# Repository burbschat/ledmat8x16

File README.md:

# *LTP-12188M-08* Based Two Color 8x16 LEDs in 8x8 Slots LED Matrix Display Module

## Motivation
Found a place that sold their dead stock of *LTP-12188M-08* modules for
extremely cheap and bought a whole bunch.
To drive those I would like to have a minimal and cheap solution which is also
modular, meaning I can build an (for any practical purposes) arbitrarily sized
display by just assembling identical modules (and perhaps a few cables etc.).

## Pictures
### Renders
Had some fun with [this incredible
tool](https://github.com/30350n/pcb2blender). Shown renders are of the first
version of the single tile driver board.
There is a newer revision with extra features for mouting as well as a *blade*
version where 8 modules are combined into one long board, as that is a much
more reasonable solution for large displays.

| Front                                                              | Back                                                              | Oblique
| ------------------------------------------------------------------ | ----------------------------------------------------------------- | ---------------------------------------------------------------------- |
|  |  |  |

### Prototype
Testing three prototype modules driven by a Raspberry Pi Pico (which is
debugged from a second Pico via SWD).
The colors do look much more vibrant in person. Also, the apparent differences
in brightness are an artifact of the way this picture was captured.

A second test now using the controller and row connect boards for a double row
display. Again, the colors look much better in person than on this picture.
This can now display much larger frames as well as animations (cycling through
a given number of frames in a buffer on the pico). For faster data transfer a
serial interface over USB is used (previously UART through the debug probe was
used, which is much slower).
A debug probe is still attached for, well, debugging. But the device now can be
used without it.

## Parts
* *LTP-12188M-08* (8x8 two-color (red/green) LED dot matrix)
* *TLC59283* (16 channel constant current LED driver with pre-charge FET)
    * Seems to be cheapest LED driver available
    * No dimming supported but perhaps possible by updating the frames at a high enough rate
    * Can be daisy chained
    * Up to 32MHz operation advertised
        * One frame is 8 rows x 16 bits = 128 transfers. At 32MHz one transfer
        takes 3.125e-08s so 4e-6s per frame per tile. For 60 tiles thats
        240e-6s for the whole panel. If we want 60 frames per second
        (16.666e-3s per frame), we can sub-divide each frame into 69 sections
        for which a pixel can be either on or off. Thus a 69 level brightness
        adjustment may be possible.
* *DMP31D7LDW-13* (dual p-channel enhancement mode MOSFET)
    * Seems to be the cheapest on DigiKey with ~500ma sustained current
    * Should switch fast enough
        * NTZD3152P may be a faster alternative, but tolerates less peak
        current (sustained currents is similar though)
* Board connectors
    * DigiKey
        * *Ph2ra-16-ua*
            * cheapest on DigiKey
            * mating connector from same manufacturer seems to be rs2br-16-g? but
            this is not readily available and of odd shape...
        * *pptc082ljbn-rc*
            * Cheapest mating connector on DigiKey
        * *Consider buying those from lcsc where they should be much cheaper*
    * LCSC
        * *2541WR-2x08P*
            * Extremely cheap
        * *PM254-2-08-W-8.5*
            * Mating part from same manufacturer: PZ254-2-08-W-8.5

### Notes
* There seems to be no cheap LED driver which supports row *and* column driving
    * IS31FL3731 seems to be pretty capable. Costs a little more but is still
    affordable. However, choosing the simpler part will surely teach one more
    things than just buying the solution.

#### LED Currents
* Use 5V supply
    * The TLC59283 are constant current and support up to 10V
        * The constant-current value of all 16 channels is set by a single external resistor
    * 3.3V may also work, but may be insufficient for some chips, so use 5V
* Peak forward current is 60mA/90mA (green/red)
    * 16 columns (8 red 8 green) on one row so peak current of 1200 mA per row
* Average current is 25mA (same for both colors)
    * Total of 400mA average current per row (if all 16 channels are on)
    * A 500mA sustained/1.2A peak driver should be sufficient
    * In actual operation the rows are multiplexed so actually only about an
    eight of the average current is expected. So actually 400mA sustained
    current per tile if all LEDs are on.
    * Eventually set the current limit at the TLC59283 to around 25mA
        * 2k resistor should give 26.5mA, which is alright
* Want row drivers separately for each tile to avoid driver current scaling
with number of tiles
    * Make sure that connections between tiles support high enough currents
* Consider [MOSFET arrays](https://www.digikey.com/en/products/filter/transistors/fets-mosfets/fet-mosfet-arrays/289)
as we need 8 of them per tile
    * Need P-channel to drive by setting gate voltage low (below source voltage)
    * Maybe not too long rise/fall times 
    * DMP31D7LDW-13 seems fine (20JPY at 200 pieces, doesn't seem to get much cheaper on digikey)
        * There are many SOT-363 options so if this one does not work, one can
        probably find a pin compatible alterative
    * [Search on digikey](https://www.digikey.jp/en/products/filter/transistors/fets-mosfets/fet-mosfet-arrays/289?s=N4IgjCBcoEwAwHYqgMZQGYEMA2BnApgDQgD2UA2iAgMwAcCALEsWDPHHCC2xzCALrEADgBcoIAMoiATgEsAdgHMQAX2IA2OLWQg0kLHiKkKIGGFoBWauq6nrNBrZj2rThq2p9iMBvHXU3ajAATgDvBiDgm2IEdVoYC2CnCwtLMNMUy21vVNiLZODguGjTdWc4p38IkpgEGGDUpwQLLUdvWlC2JyKEUO6YeLbTYIGE7uCwFNswEIQ62wZaScSFsGavEHdm9MXl7M2WmlsWos5iCwGwEpS4d2OWxvPGanTE53TNEYgNWvrp9WawSGV1iYHSrABYGBMEh%2B1YtCY%2BW4CLm01qCCWaOCtABWPo33AQSsBLBkwYwKJDCSLBe7g2YIYiTh1g4JTBdQq3jgkyBTm5ZXS8CuL2mCHMCNFAz6LDqHTZssKouoUWBjCiJLV8xlmkx2q08o5SJA8TycIxMKNayKUxl1up4FovGYDo4nictRCGzYdUQfM0NtMxTgFmd2xoBL8jpqiHJ9vgjBWXPidD5gyGvVY5lTCSN8BGCDOpjA3LBTmLM2dZmK8TLYM5RfZhZ8c2Kbjm1CGzcYleoWi0TiC1F6tlo1CsZQHzhCk5xPYY3M7HfccfUZXUEdXA32MP8t2S9VxOXnk2STHnp8YEcdBe3cVojsqIwf3gL7kFr66L7Wve6Q58v5oXNQnWJxRwRDZe0WRViEg61bFiVdfRg25QjjKIUiGHF6GdfwrUtBl1GBXw4CKf4ZjWaZRypcFRxaQtzDHeBklXGYBGEMRIEkGQFGUNQQAAWj4aBdCgGQAFcjDISBKCNJJ%2BD4-ikmEvRxMkkwIHkvibGE2QABNxH48tbFEcRbBEABPIR8HETBcDQFQVCAA)

#### Clock
The clock will have to arrive at each TLC59283 before the output of the
previous one had a chance to change. According to the data sheet, the delay
until SOUT changes is normally around 11ns. As we are only concerned about
adjacent modules in close proximity, the clock propagation delay should be well
below 10ns.
A possible concern mentioned [here](https://www.eevblog.com/forum/projects/shift-register-delay-tlc59283/msg5714097/#msg5714097)
is that the clock signal integrity may be degraded due to large capacitance if
we fan it out too far. To solve this we may employ a buffer, this however would
mean we need either a very fast buffer to not skew the clock relative to the
data signal too much, or also have to buffer the data signal at the same time.
Buffering two signals should be doable.
This is probably not an issue, but technically if the buffers are to slow, this
could limit the rate at which we can operate the panel (i.e. clock in data).
As, if it works, no buffers should be the easier solution, for now I'll try
without. If required, we may try to add clock line terminations to avoid
ringing.

## Mechanical Design
* Board interconnects using horizontal pin headers on the back of the board (tile is on the front)
    * 8 pins seem to fit just right, so two rows with 8 pins each seems to be a good choice
    * These also will provide mechanical support within each row
* Consider some sort of locating feature to use to locate modules in maybe a
3d-printed back plane or with small clips to be inserted between modules (**TODO**) 
    * Could shave off the corners and have short square (45 deg. rotated) posts on the back plane
    * High symmetry is probably a good thing so locating features on maybe only
    top/bottom may not be as useful as the shaved off corners
    * To assemble multiple rows such a locating feature would be required
    * For a large display with many rows and columns a backplane is probably mandatory
    
## Heat Dissipation
Found that when I run a fully lit frame (all 16 LEDs enabled while multiplexing
the rows) the whole module gets quite hot. Not entirely sure what produces the
heat. If it is the TLC59283, one could simply remove the solder mask on the
back side of the board which is a ground plane to which the ground pad on the
TLC59283 is connected to and place some sort of heat sink there.
This is of course the reason why the TLC59283 is placed under the LED matrix
module on the front and not at the back of the board and not simply attributed
to be not checking the orientation of the modules footprint before doing the
tedious routing which I do not want to do twice.
Will have to further check what is the source of the heat. However, as long as
the display is not constantly fully illuminated, it does not appear to get
excessively hot.

## Driving the Modules
I use an Raspberry Pi Pico (2 to be exact) to the modules. The serial interface
for the TLC59283 is implemented using a PIO state machine (with DMA) which can
clock out serial data independent of the processor cores and thus is a very
performant solution. Switching between the rows is done by the processor which
also feeds data from a global frame buffer to the DMA (which feeds it to the
PIO state machine).
Other microcontrollers will probably also work. Not sure how one would handle
the serial communication though. AT a slower rate one can perhaps just bit bang
using GPIO. Didn't try.
The code I use on the Pico is available in a separate repository [here](https://github.com/burbschat/ledmat8x16pico/).

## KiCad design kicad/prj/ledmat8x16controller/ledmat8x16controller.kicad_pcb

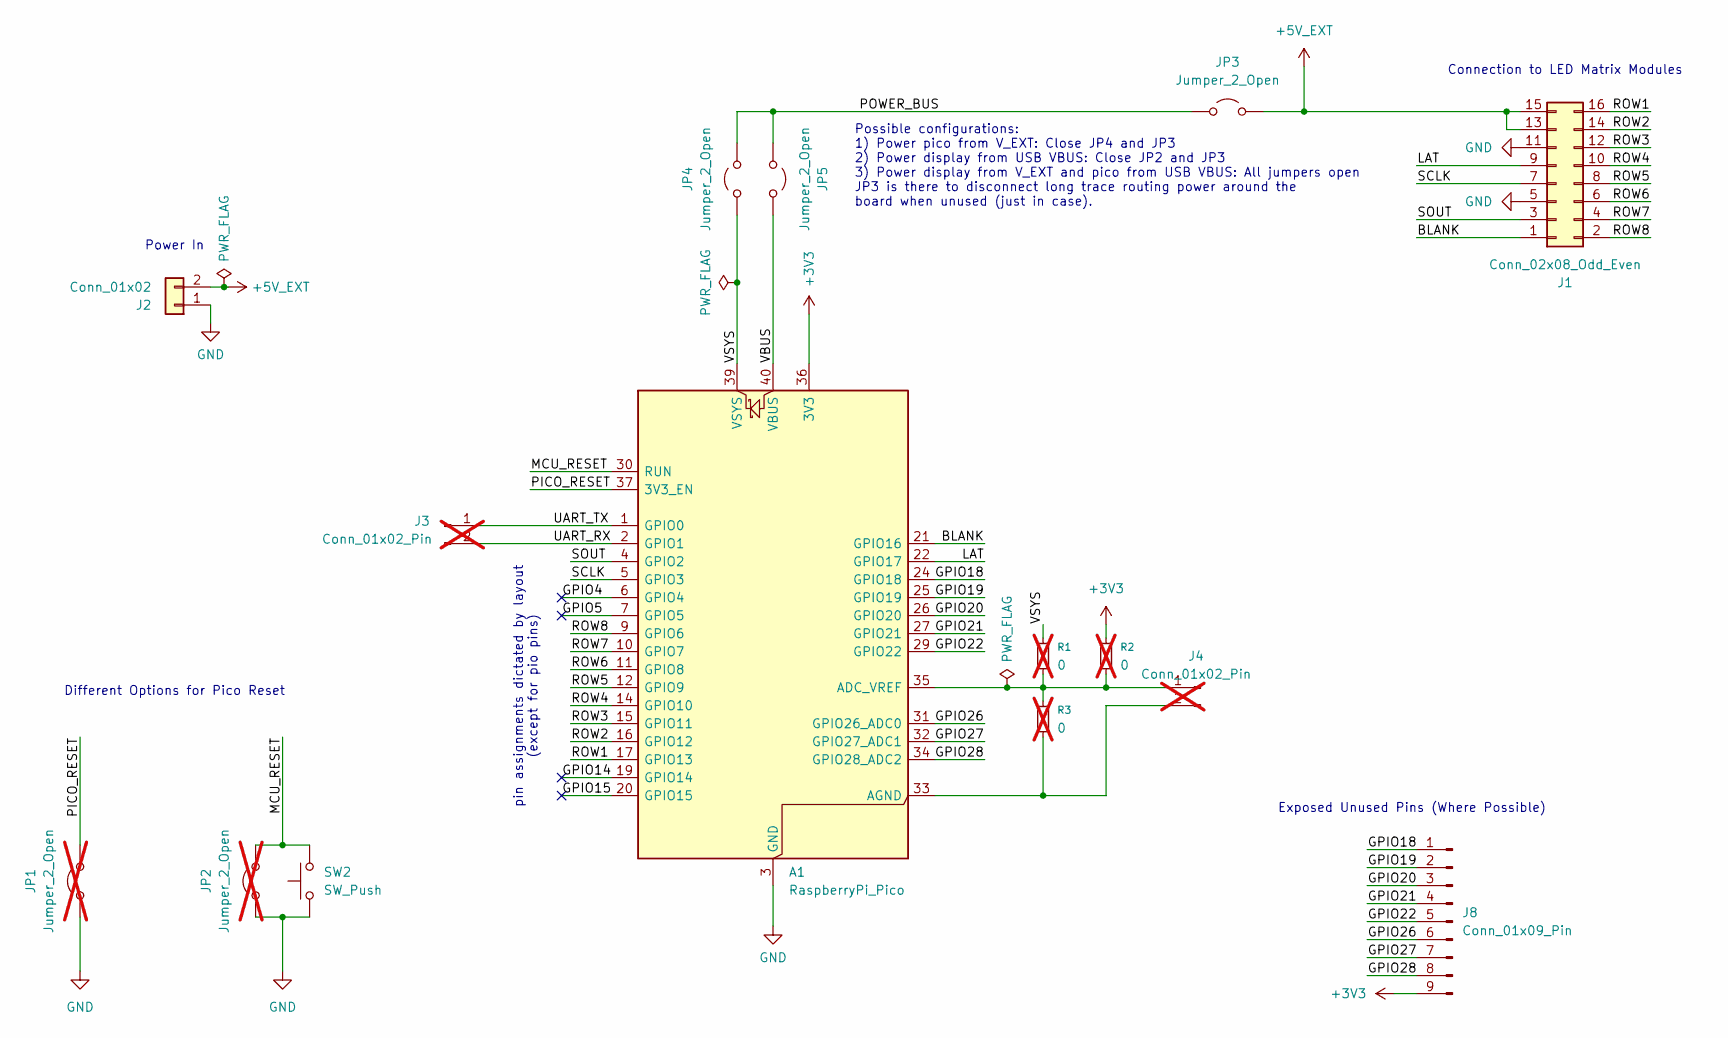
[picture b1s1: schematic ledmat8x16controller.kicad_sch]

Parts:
A1: RaspberryPi_Pico; RaspberryPi_Pico_Common_ProbablySocketed
J1: Conn_02x08_Odd_Even; PinSocket_2x08_P2.54mm_Horizontal
J2: Conn_01x02; TerminalBlock_Phoenix_PT-1,5-2-3.5-H_1x02_P3.50mm_Horizontal
J3, J4: Conn_01x02_Pin; PinHeader_1x02_P2.54mm_Vertical; not fitted
J8: Conn_01x09_Pin; PinHeader_1x09_P2.54mm_Vertical
JP1, JP2: Jumper_2_Open; TestPoint_2Pads_Pitch2.54mm_Drill0.8mm; not fitted
JP3, JP4, JP5: Jumper_2_Open; SolderJumper-2_P1.3mm_Open_RoundedPad1.0x1.5mm
R1, R2, R3: 0; R_0603_1608Metric_Pad0.98x0.95mm_HandSolder; not fitted
SW2: SW_Push; SW_SPST_SKQG_WithStem

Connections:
+3V3: A1.36 (3V3), J8.9, R2.1
+5V_EXT: J1.13, J1.15, J2.2, JP3.2 (B)
/BLANK: A1.21 (GPIO16), J1.1
/GPIO4: A1.6 (GPIO4)
/GPIO4_1: A1.6 (GPIO4)
/GPIO5: A1.7 (GPIO5)
/GPIO5_1: A1.7 (GPIO5)
/GPIO14: A1.19 (GPIO14)
/GPIO14_1: A1.19 (GPIO14)
/GPIO15: A1.20 (GPIO15)
/GPIO15_1: A1.20 (GPIO15)
/GPIO18: A1.24 (GPIO18), J8.1
/GPIO19: A1.25 (GPIO19), J8.2
/GPIO20: A1.26 (GPIO20), J8.3
/GPIO21: A1.27 (GPIO21), J8.4
/GPIO22: A1.29 (GPIO22), J8.5
/GPIO26: A1.31 (GPIO26_ADC0), J8.6
/GPIO27: A1.32 (GPIO27_ADC1), J8.7
/GPIO28: A1.34 (GPIO28_ADC2), J8.8
/LAT: A1.22 (GPIO17), J1.9
/MCU_RESET: A1.30 (RUN), JP2.2 (B), SW2.2
/PICO_RESET: A1.37 (3V3_EN), JP1.2 (B)
/POWER_BUS: JP3.1 (A), JP4.2 (B), JP5.2 (B)
/ROW1: A1.17 (GPIO13), J1.16
/ROW2: A1.16 (GPIO12), J1.14
/ROW3: A1.15 (GPIO11), J1.12
/ROW4: A1.14 (GPIO10), J1.10
/ROW5: A1.12 (GPIO9), J1.8
/ROW6: A1.11 (GPIO8), J1.6
/ROW7: A1.10 (GPIO7), J1.4
/ROW8: A1.9 (GPIO6), J1.2
/SCLK: A1.5 (GPIO3), J1.7
/SOUT: A1.4 (GPIO2), J1.3
/UART_RX: A1.2 (GPIO1), J3.2
/UART_TX: A1.1 (GPIO0), J3.1
/VBUS: A1.40 (VBUS), JP5.1 (A)
/VSYS: A1.39 (VSYS), JP4.1 (A), R1.1
GND: A1.3 (GND), A1.8 (GND), A1.13 (GND), A1.18 (GND), A1.23 (GND), A1.28 (GND), A1.38 (GND), J1.5, J1.11, J2.1, JP1.1 (A), JP2.1 (A), SW2.1
unnamed: A1.35 (ADC_VREF), J4.1, R1.2, R2.2, R3.1
unnamed: A1.33 (AGND), J4.2, R3.2

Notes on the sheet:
Exposed Unused Pins (Where Possible)
Connection to LED Matrix Modules
Possible configurations: 1) Power pico from V_EXT: Close JP4 and JP3 2) Power display from USB VBUS: Close JP2 and JP3 3) Power display from V_EXT and pico from USB VBUS: All jumpers open JP3 is there to disconnect long trace routing power around the board when unused (just in case).
pin assignments dictated by layout (except for pio pins)
Power In
Different Options for Pico Reset

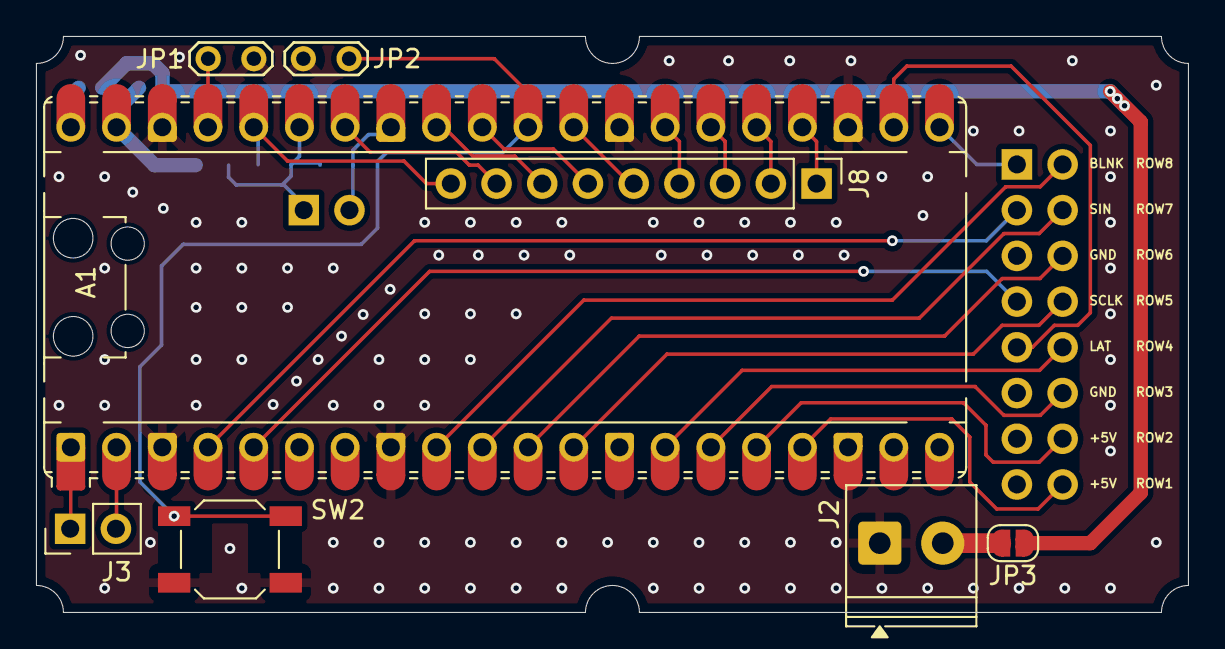
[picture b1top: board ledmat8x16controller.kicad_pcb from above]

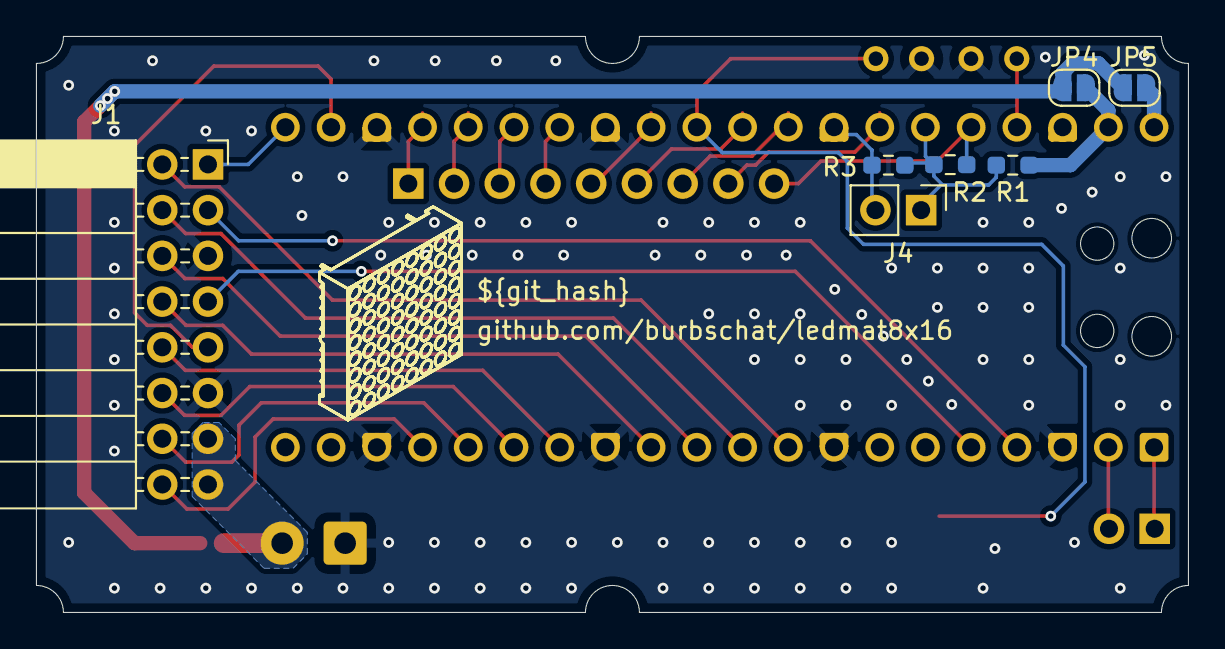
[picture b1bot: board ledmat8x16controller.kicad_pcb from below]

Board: 2 copper layers, 64.0 x 32.0 mm, 15 parts (7 on the bottom side), 32 nets.

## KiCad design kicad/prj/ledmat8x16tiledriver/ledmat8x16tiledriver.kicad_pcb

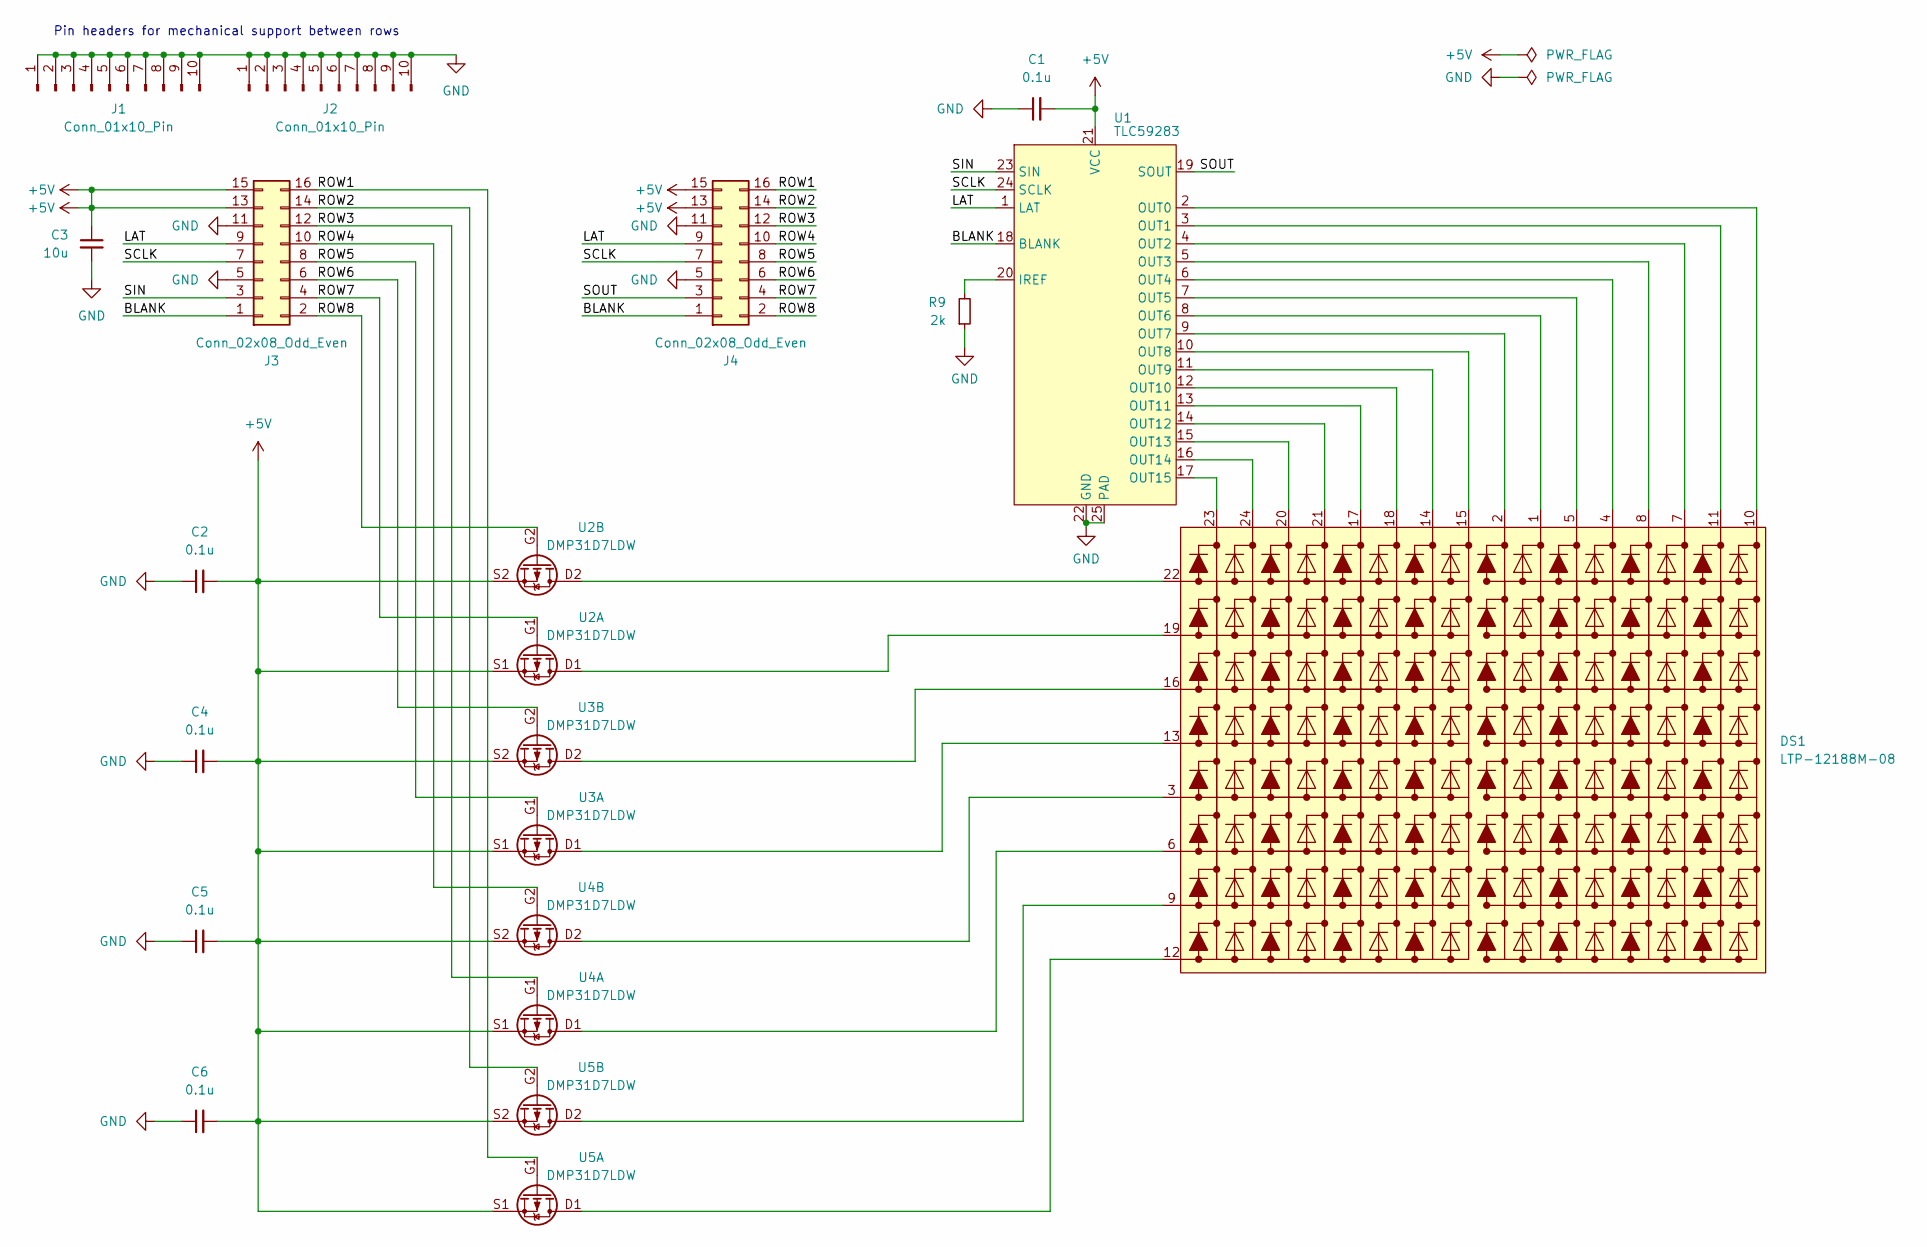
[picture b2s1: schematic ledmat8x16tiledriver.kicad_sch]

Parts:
C1, C2, C4, C5, C6: 0.1u; C_0603_1608Metric_Pad1.08x0.95mm_HandSolder
C3: 10u; C_0805_2012Metric_Pad1.18x1.45mm_HandSolder
DS1: LTP-12188M-08
J1, J2: Conn_01x10_Pin; PinHeader_1x10_P2.54mm_Vertical
J3: Conn_02x08_Odd_Even; PinHeader_2x08_P2.54mm_Horizontal
J4: Conn_02x08_Odd_Even; PinSocket_2x08_P2.54mm_Horizontal
R9: 2k; R_0603_1608Metric_Pad0.98x0.95mm_HandSolder
U1: TLC59283; Texas_RGE0024C_VQFN-24-1EP_4x4mm_P0.5mm_EP2.1x2.1mm
U2, U3, U4, U5: DMP31D7LDW; SOT-363_SC-70-6

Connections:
+5V: C1.2, C2.2, C3.1, C4.2, C5.2, C6.2, J3.13, J3.15, J4.13, J4.15, U1.21 (VCC), U2.S1, U2.S2, U3.S1, U3.S2, U4.S1, U4.S2, U5.S1, U5.S2
/BLANK: J3.1, J4.1, U1.18 (BLANK)
/LAT: J3.9, J4.9, U1.1 (LAT)
/ROW1: J3.16, J4.16, U5.G1
/ROW2: J3.14, J4.14, U5.G2
/ROW3: J3.12, J4.12, U4.G1
/ROW4: J3.10, J4.10, U4.G2
/ROW5: J3.8, J4.8, U3.G1
/ROW6: J3.6, J4.6, U3.G2
/ROW7: J3.4, J4.4, U2.G1
/ROW8: J3.2, J4.2, U2.G2
/SCLK: J3.7, J4.7, U1.24 (SCLK)
/SIN: J3.3, U1.23 (SIN)
/SOUT: J4.3, U1.19 (SOUT)
GND: C1.1, C2.1, C3.2, C4.1, C5.1, C6.1, J1.1, J1.2, J1.3, J1.4, J1.5, J1.6, J1.7, J1.8, J1.9, J1.10, J2.1, J2.2, J2.3, J2.4, J2.5, J2.6, J2.7, J2.8, J2.9, J2.10, J3.5, J3.11, J4.5, J4.11, R9.1, U1.22 (GND), U1.25 (PAD)
unnamed: DS1.3, U4.D2
unnamed: DS1.6, U4.D1
unnamed: DS1.9, U5.D2
unnamed: DS1.12, U5.D1
unnamed: DS1.13, U3.D1
unnamed: DS1.16, U3.D2
unnamed: DS1.19, U2.D1
unnamed: DS1.22, U2.D2
unnamed: R9.2, U1.20 (IREF)
unnamed: DS1.10, U1.2 (OUT0)
unnamed: DS1.11, U1.3 (OUT1)
unnamed: DS1.7, U1.4 (OUT2)
unnamed: DS1.8, U1.5 (OUT3)
unnamed: DS1.4, U1.6 (OUT4)
unnamed: DS1.5, U1.7 (OUT5)
unnamed: DS1.1, U1.8 (OUT6)
unnamed: DS1.2, U1.9 (OUT7)
unnamed: DS1.15, U1.10 (OUT8)
unnamed: DS1.14, U1.11 (OUT9)
unnamed: DS1.18, U1.12 (OUT10)
unnamed: DS1.17, U1.13 (OUT11)
unnamed: DS1.21, U1.14 (OUT12)
unnamed: DS1.20, U1.15 (OUT13)
unnamed: DS1.24, U1.16 (OUT14)
unnamed: DS1.23, U1.17 (OUT15)

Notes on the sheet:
Pin headers for mechanical support between rows

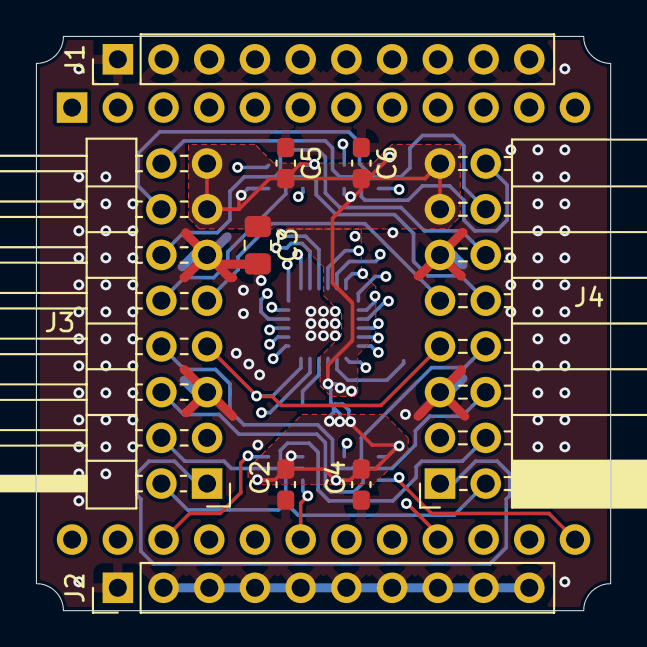
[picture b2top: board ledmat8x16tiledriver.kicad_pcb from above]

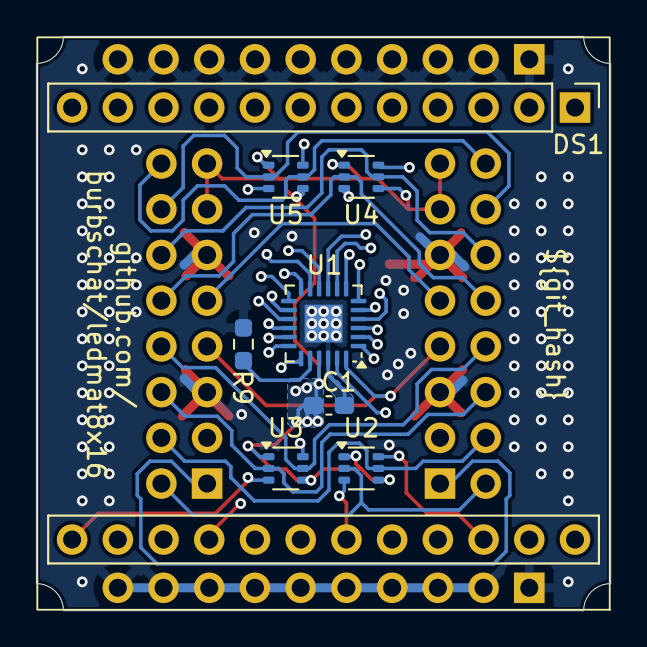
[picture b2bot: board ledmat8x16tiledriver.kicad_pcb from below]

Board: 4 copper layers, 31.9 x 31.9 mm, 17 parts (8 on the bottom side), 40 nets.

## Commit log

2025-03-23 initial notes and collection of datasheets
2025-03-24 draw basic schematic
    some footprint assignment is still todo
2025-03-24 create/assign all footprints
2025-03-27 finish layout (witch a catch)
    I put the led matrix footprint on the wrong side of the board...
    This was fixed by moving the pin headers which however now results in
    the controller IC being under the led matrix module. Not what I wanted
    but not easy to fix. I wanted to use headers to mount the module anyways
    to there should be no interference. Try to use some short female pin
    headers (which apparently is a thing).
2025-04-13 re-route traces close to clock trace
    Clock appeared to couple into the closeby traces
2025-04-13 attempt to increase space between data and blank traces
    also observed coupling of data into the blank line.
2025-05-03 Fix empty value field for TLC59283
2025-05-03 Add 3d model for led matrix module
2025-05-03 Add 3d model for socketed version of the led matrix module
2025-05-03 Add license
2025-05-03 Add kibot config file
2025-05-03 Add some renders of the PCB
2025-05-03 Add another picture to readme and adjust layout of renders
2025-05-03 Adjust README title
2025-05-13 Fix wrong footprint type for led matrix module
2025-05-13 Update footprints in layout (including the led matrix module one)
2025-05-13 Cut little arcs into the corners for mounting modules with maybe M3 screws
    Or perhaps standoffs?
2025-05-13 Fix led modules footprint througholes out of alignment by 0.01mm
    Of course this does not really matter, but it bugs me.
2025-05-13 Add some holes for headers near the top/bottom edge
    Perhaps this can be used as a different way of mounting. Not sure, I'll
    have to try. Unfortunately the board dimensions did not allow for the
    spacing to be a multiple of 2.54mm. But positioning is such that between
    adjacent rows the headers should be exactly 2.54mm apart.
2025-05-13 Update small resistor symbol to match library
2025-05-16 Slight adjustments to zone fill and ground plane
2025-05-16 Update footprint to newer version (with smaller courtyard)
2025-05-16 Add repo url and git hash to silkscreen
    For traceability, but also just becasue it's possible.
    Substitution of git hash is done by kibot.
2025-05-18 Add files for a simple row interconnect board
2025-05-18 Indicate some of the important dimensions on the user drawings layer
2025-05-18 Add dimensions to interconnect board, fix silkscreen
2025-05-18 Fix slight asymetry in zone fill
2025-05-23 Add rasperry pi pico library repo as submodule
2025-05-23 Add footprint and symbol library tables to interconnect project
2025-05-31 Throw together a pico breakout board
    Not very sophisticated at all, but probably will do the job (which is to
    avoid having to connect all the lines separately using jumper wires).
2025-08-03 Combine 8 modules into a single "blade" pcb
    This allows for fewer connectors with large displays.
    A "blade" is "hackable" in the sense of cutting it up into separate
    modules which should still function on their own.
2025-08-03 Add missing kibot config
2025-08-03 Resize controller board to 32mm outline
2025-08-03 Resize row-connect board to 32mm outline
2025-08-04 Add missing git hash silkscreen to controller board
2025-10-19 Update README with a new picture and some extra information
2025-11-02 Rework the controller (pico carrier) board
    Previous version was thrown together in a short time as I was ordering
    boards anyways and wanted to test the concept for a pico carrier thing.
2025-11-02 Additions to silkscreen
2025-11-02 Add svgs used on silkscreen
2025-11-02 Change all led module modules to socketed 3d model on blade board
2025-11-02 Change headers for mounting to dnp on blade pcb
2025-11-02 Fix socketed module 3d model socket pin color
    (and some broken links)
